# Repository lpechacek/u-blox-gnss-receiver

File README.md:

# u-blox-gnss-receiver
Document about design of a Bluetooth GNSS receiver.

Keywords: GNSS, Bluetooth, Android, GPS, GLONASS, BeiDou, Galileo

This work is licensed under a [Creative Commons Attribution 4.0 International License](http://creativecommons.org/licenses/by/4.0/).

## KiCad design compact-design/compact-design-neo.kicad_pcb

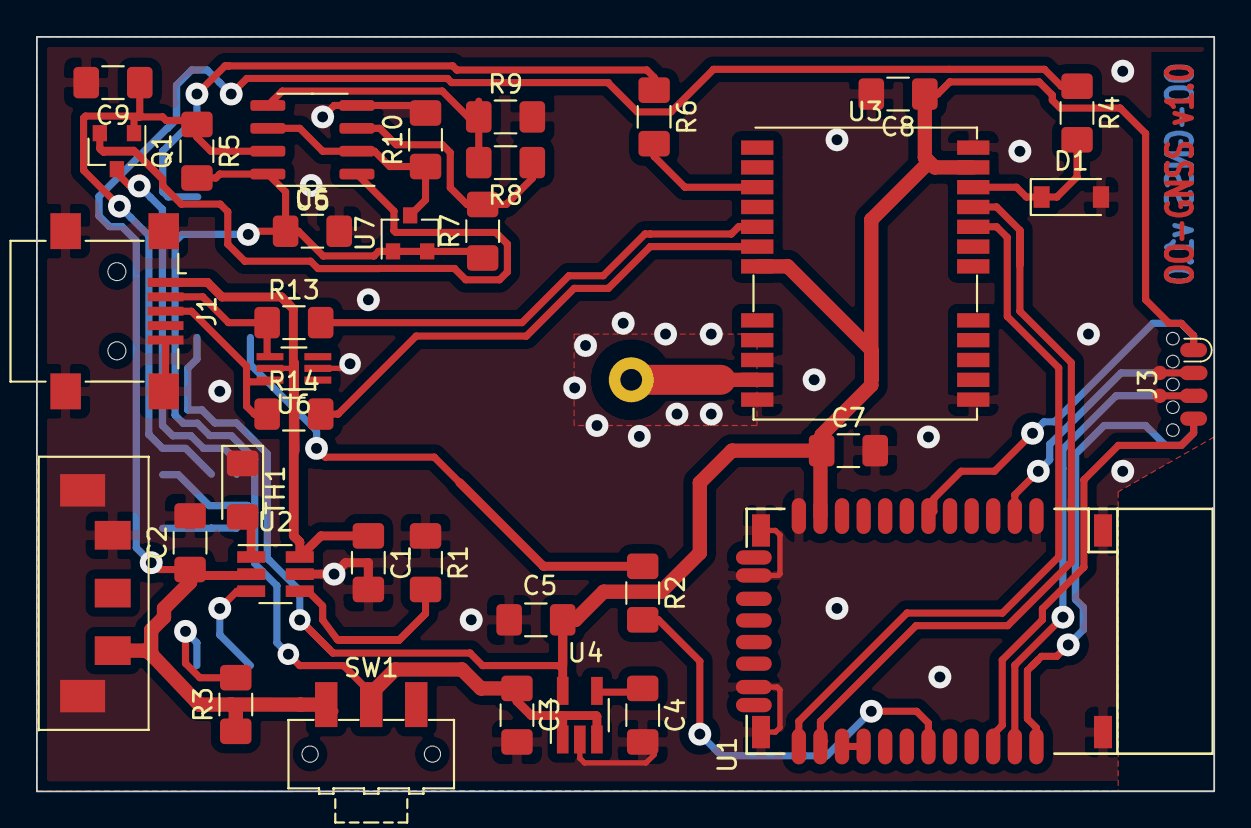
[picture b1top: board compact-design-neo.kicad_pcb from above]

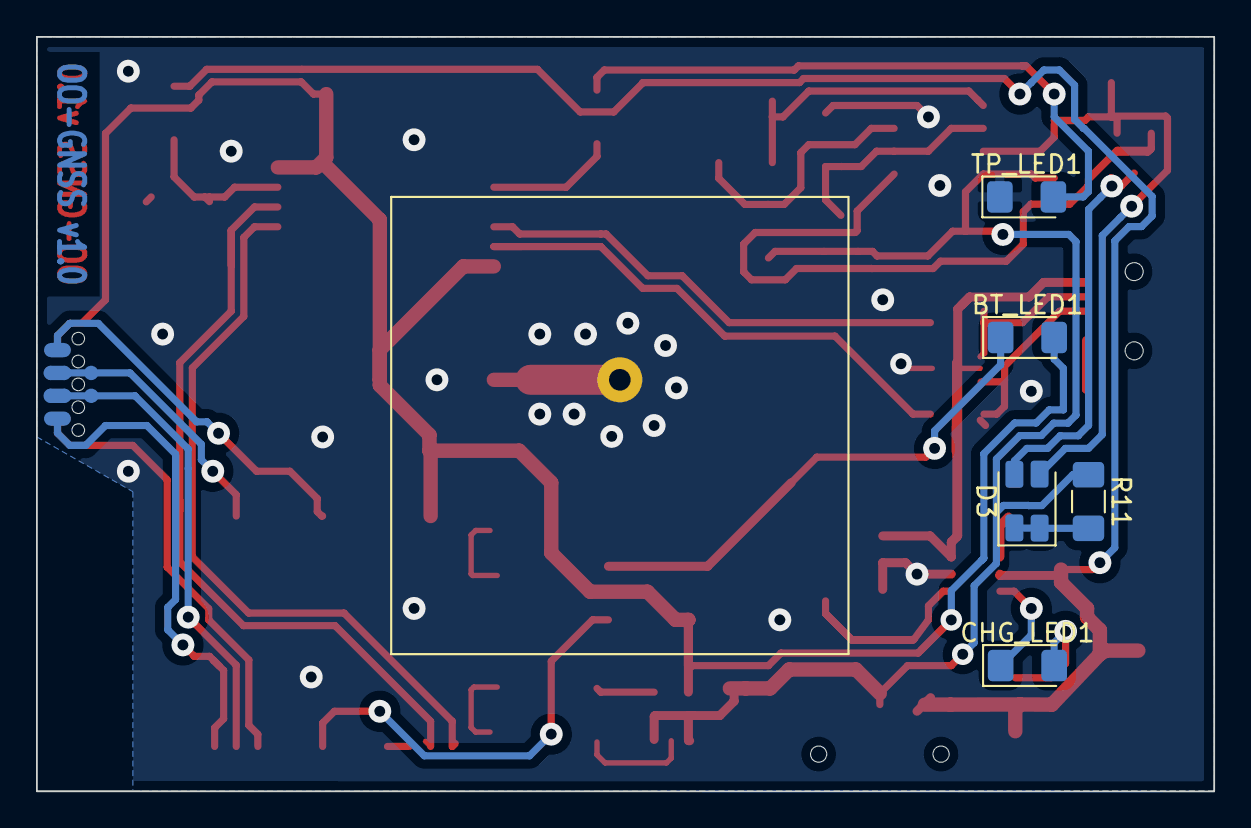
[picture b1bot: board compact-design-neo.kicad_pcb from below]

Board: 2 copper layers, 65.4 x 41.9 mm, 41 parts (6 on the bottom side), 35 nets.

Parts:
AE1: Taoglas CGPP.25.4.E.02; gnss-patch-25x25
BT_LED1: LED; LED_1206_3216Metric_Pad1.42x1.75mm_HandSolder
C1, C2, C3: 1uF; C_1206_3216Metric_Pad1.42x1.75mm_HandSolder
C4: 10nF; C_1206_3216Metric_Pad1.42x1.75mm_HandSolder
C5: 4.7uF; C_1206_3216Metric_Pad1.42x1.75mm_HandSolder
C6, C7, C8, C9: 100nF; C_1206_3216Metric_Pad1.42x1.75mm_HandSolder
CHG_LED1: LED; LED_1206_3216Metric_Pad1.42x1.75mm_HandSolder
D1: 3V3; D_SOD-123
D3: HSMF-C15A; LED_DUAL_1210_3225Metric_Pad1x1.5mm_HandSolder
J1: USB_C_Receptacle_USB2.0; USB_Mini-B_Lumberg_2486_01_Horizontal
J3: SOICbite; SOIC_clipProgSmall
J4: TE 1981061-1; connector-TE_1981061-1
Q1: BSS138; SOT-23
R1: 1k2; R_1206_3216Metric_Pad1.42x1.75mm_HandSolder
R2, R6: 1k; R_1206_3216Metric_Pad1.42x1.75mm_HandSolder
R3: 1k5; R_1206_3216Metric_Pad1.42x1.75mm_HandSolder
R4: 64k; R_1206_3216Metric_Pad1.42x1.75mm_HandSolder
R5: 100k; R_1206_3216Metric_Pad1.42x1.75mm_HandSolder
R7: 39k; R_1206_3216Metric_Pad1.42x1.75mm_HandSolder
R8: 2k4; R_1206_3216Metric_Pad1.42x1.75mm_HandSolder
R9: 15k; R_1206_3216Metric_Pad1.42x1.75mm_HandSolder
R10: 560; R_1206_3216Metric_Pad1.42x1.75mm_HandSolder
R11: 100; R_1206_3216Metric_Pad1.42x1.75mm_HandSolder
R13, R14: 27; R_1206_3216Metric_Pad1.42x1.75mm_HandSolder
SW1: JS102011SAQN; SW_SPDT_CK-JS102011SAQN
TH1: Thermistor_NTC; D_1206_3216Metric_Pad1.42x1.75mm_HandSolder
TP_LED1: LED; LED_1206_3216Metric_Pad1.42x1.75mm_HandSolder
U1: RN42
U2: BQ21040; SOT-23-6_Handsoldering
U3: NEO-M8N; ublox_NEO
U4: LP2985-3.3; SOT-23-5_HandSoldering
U5: LM293; SOIC-8_3.9x4.9mm_P1.27mm
U6: TPD4E001DCKR; SOT-363_SC-70-6_Handsoldering
U7: TL431AIDBZ; SOT-23

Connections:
+3V3: BT_LED1.2, C5.1, C7.1, C8.1, J3.1, U1.11, U3.7, U3.23, U4.5
/BatteryPower: C2.1, J4.1, R3.1, R4.1, SW1.1, U2.2
/D+: J1.3, R14.1, U6.6
/D-: J1.2, R13.1, U6.4
/FromSwitch: C3.1, C6.1, R5.2, R7.1, R11.1, SW1.2, U4.1, U4.3, U5.8, U7.1, U7.2
/PowerInput: C1.1, J1.1, U2.6, U6.5
/RN42_CLK: J3.8, U1.6
/RN42_CS: J3.6, U1.23
/RN42_FACT_DEF: J3.4, U1.22
/RN42_MISO: J3.5, U1.24
/RN42_MOSI: J3.7, U1.2
/USB_D+: R14.2, U3.6
/USB_D-: R13.2, U3.5
GND: C1.2, C2.2, C3.2, C4.2, C5.2, C6.2, C7.2, C8.2, C9.2, D1.2, J1.5, J1.6, J3.2, J3.3, J4.3, R1.1, R9.2, R10.2, TH1.1, TP_LED1.1, U1.1, U1.12, U1.28, U1.29, U1.36, U2.5, U3.10, U3.12, U3.13, U3.24, U4.2, U5.4, U6.2
unnamed: AE1.1, U3.11
unnamed: BT_LED1.1, R2.1
unnamed: C4.1, U4.4
unnamed: C9.1, D3.4, Q1.1, R5.1, U5.7
unnamed: CHG_LED1.1, U2.3
unnamed: CHG_LED1.2, R3.2
unnamed: D1.1, R4.2, U3.22
unnamed: D3.1, D3.3, R11.2
unnamed: D3.2, Q1.3
unnamed: Q1.2, U5.1
unnamed: R1.2, U2.4
unnamed: R2.2, U1.19
unnamed: R6.1, TP_LED1.2
unnamed: R6.2, U3.3
unnamed: R7.2, R8.1, U5.3
unnamed: R8.2, R9.1, U5.5
unnamed: R10.1, U5.2, U5.6, U7.3
unnamed: TH1.2, U2.1
unnamed: U1.13, U3.20
unnamed: U1.14, U3.21
unnamed: U1.15, U1.16

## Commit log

2019-01-04 Rearranged pictures, fixed typos
2019-01-11 Software and receiver configuration
2019-01-16 Final arrangements for first document release
2019-12-29 Compact receiver design
    Basically the same design again with charger circuit, voltage regulator and
    battery charge indicator on one board.
2020-01-31 u-blox-gnss-receiver: Add Lessons Learned
    Document lessons learned about power bank selection and the misbehavior of the
    on-board memory backup battery.
2020-05-28 Compact receiver design: Updated schematics
    This schematic embodies the lessons learned from the first prorotype. It
    eliminates a few apparent bugs and switches to an actie antenna. In
    reality the Bluetooth module generated enough noise to completely block
    GNSS reception. Using a detachable active antenna with an additional SAW
    filter solves the problem.

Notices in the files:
README.md:
CC BY Icon
